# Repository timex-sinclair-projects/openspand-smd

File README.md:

# OpenSpand Card

A chip-down, surface-mount [OpenSpand](https://codeberg.org/NollKollTroll/OpenSpand), the
open-source all-in-one expansion for the Sinclair ZX81, on a card that stands upright in
an edge socket on a ZX81 expansion bus. It's designed for JLCPCB assembly.

The card is 155 × 57 mm, close to the ZX81's width, so a row of cards fits a 3D-printed
case behind the computer. The ZX81's own 23-position edge (key slot at position 3) is cut
along the bottom as gold fingers, 6.38 mm in from the right edge so they line up with the
ZX81's connector. All the SMD parts are on the component side, which faces the ZX81.

| Edge | Connectors |
| --- | --- |
| Left | SPI header (top); DE-9 joystick |
| Right | microSD (card goes in from the side); HDMI (DVI picture, HDMI sound) below it |
| Top | red and green status LEDs (3 mm, hand-fitted, looking up out of the edge); RESET, CONFIG, BOOTSEL and RUN buttons (right-angle, hand-fitted, pushed from above); USB-C |
| Bottom | ZX81 fingers |

**Status: unverified prototype (rev 0.2), fully routed.** Rev 0.2 replaces rev 0.1's VGA
socket with DVI on an HDMI socket, driven by the RP2350's HSTX block, and sends sound over
HDMI ([issue 7](https://github.com/timex-sinclair-projects/openspand-smd/issues/7)). ERC is
clean, the PCB matches the schematic, and DRC shows no clearance, edge or unconnected
errors (only silkscreen warnings). No board has been built, and the firmware patch
deliberately doesn't build until the DVI and HDMI-audio code is written. Review it before
you order.

The full write-up (form factor, finger convention, routing results, regenerating) is in
[card/README.md](card/README.md).

## From modules to chips

Upstream V1.31 is built from plug-in modules plus through-hole parts. The card puts the
chips themselves on a 4-layer board:

| Function | Upstream V1.31 | OpenSpand Card |
| --- | --- | --- |
| MCU | Olimex Pico2-XL module | RP2350B + W25Q128JV 16 MB flash + Abracon ABM8-272-T3 12 MHz crystal |
| 3.3 V | regulator on module | ME6211C33 LDO |
| 1.2 V core | RP2350 switcher + inductor on module | ME6211C12 LDO (no inductor) |
| USB | on module | USB-C, BOOTSEL and RUN buttons |
| RTC | DS1307 module | DS3231MZ (built-in resonator, no crystal) + CR2032 |
| Settings EEPROM (0x50) | AT24C32 on RTC module | FT24C32A |
| I/O expander (0x27) | MCP23009 DIP-18 | MCP23009 SSOP-20 (same chip: 5 V-tolerant open-drain joystick inputs) |
| Audio | UDA1334 module | HDMI audio (firmware not written yet) |
| Composite video | pin header | DVI on an HDMI socket, 60 Hz, via HSTX (firmware not written yet) |
| SD card | full-size SD | microSD (TF-01A push-push) |
| 5 V joystick jumpers | pin-header jumpers | solder jumpers JP1, JP2 (open by default) |
| Serial port | UART header | none (no GPIO left) |

The DS3231MZ answers at the DS1307's address (0x68) with the same time and date
registers, so the firmware's clock code runs unchanged. It shares the I2C bus and pull-ups
with the EEPROM and I/O expander. The CR2032 is only a backup cell; nothing charges it.

## Firmware

The card needs the upstream OpenSpand_SW 0.51.0 firmware with
[card/firmware/card-pins.patch](card/firmware/card-pins.patch) applied, plus a DVI and
HDMI-audio driver that hasn't been written yet. Until then the patch fails to build, on
purpose (see [card/README.md](card/README.md#firmware)). The fingers are on the same side
as the RP2350B, and HSTX, the RP2350's only route to DVI, is fixed to GPIO12..19, so the
card puts the Z80 bus on different GPIOs from upstream:

| GPIO | Card |
| --- | --- |
| 0–7 | D0–D7 |
| 8–11 | A0–A3 |
| 12–19 | HSTX: DVI to the HDMI socket |
| 20–31 | A15–A4 (reversed) |
| 32–39 | HALT, MREQ, IORQ, RD, WR, RESET, M1, RFSH |
| 40–47 | Z80 clock (buffered), green LED, I2C, microSD |

Data still reads as the low byte of the GPIO register, as upstream does. The address comes
from one read of the low register, with a shift for A0..A3 and an RBIT for A4..A15.
GPIO40–47 are the RP2350B's ADC pins, which aren't 5 V tolerant, and the 32 bus lines use
up every other GPIO, so the ZX81's clock reaches GPIO40 through a 74LVC3G34 buffer.

The I2S DAC, its line-out jack and the serial port are gone: HSTX's eight pins took theirs.
The joystick's I/O expander, the clock and the settings EEPROM are unchanged on I2C.

## Ordering from JLCPCB

- **PCB**: upload `card/hardware/fab/OpenSpand-Card-gerbers.zip`. Choose 4 layers, 1.6 mm,
  any colour, and **gold fingers with a 45° bevel**. The tongue has no vias or pour and the
  inner planes stop at the body, so the bevel only cuts the fingers' ends.
- **Assembly**: top side. Upload `BOM-JLCPCB.csv` and `CPL-JLCPCB.csv`, then check every
  part's rotation in JLC's preview, especially U2, U3, U4, U8, U9, U10, U11, J3, J5 and J8.
- **Hand-fit** (`hand-solder.csv`): the DE-9 (J4), the four buttons (SW1–SW4, C&K
  PTS645VL83-2 LFS), the two 3 mm LEDs (D3, D4; bend the legs 90° so they look up out of the
  top edge) and the optional pin header. JLC fits the HDMI socket (J8, Molex
  208658-1001, LCSC C916313).

### Before ordering, check

- **Finger alignment**: the 6.38 mm offset assumes the ZX81's board is centred in its case.
  Measure from the case's right side to the end of the edge connector, subtract 6 mm, set
  `RIGHT_OVERHANG` in `card/tools/gen_pcb.py` and regenerate.
- **Backplane spacing**: the DE-9 stands about 12.5 mm off the board, so sockets on the bus
  need roughly 15 mm or more between them.
- **RP2350 support circuit**: the crystal (ABM8-272-T3, 15 pF load caps, 1 kΩ series
  resistor) follows Raspberry Pi's *Hardware design with RP2350*. The core supply doesn't: the
  on-chip switching regulator is unused (no inductor, VREG_LX open, VREG_FB grounded) and an
  ME6211C12 LDO (U9) feeds DVDD at 1.2 V, as in section 6.3.7 of the RP2350 datasheet. JLC
  may show its generic warning about following Raspberry Pi's guide.
- **HDMI socket**: J8 uses KiCad's footprint for the Molex 208658-1001 (LCSC C916313), with
  its "PCB Edge" line on the board edge. Compare it with Molex's drawing, and check that the
  mouth clears a case wall.
- **TMDS routing**: the eight DVI lines are 0.15 mm tracks over the GND plane, matched
  within a pair but not impedance-controlled. That's normal for GPIO-driven DVI at 640 x 480
  (252 Mbit/s per lane), but no board has been tested.
- **ESD arrays**: U10 and U11 are TI TPD4E05U06DQAR (C138714), flow-through: each TMDS line
  runs straight across a pad pair (1-10, 2-9, 4-7, 5-6).
- **Coin cell**: fit a CR2032 in BT1 after assembly; the board ships without one.
- **Buttons**: SW1–SW4 are C&K PTS645VL83-2 LFS right-angle through-hole switches, marked
  DNP so JLC skips them; buy them from Digi-Key or Mouser (LCSC has only the short-plunger
  PTS645VK39) and solder them yourself.
- **Low-stock parts**: MCP23009T-E/SS (C629436) and FT24C32A (C232883) had a few hundred in
  stock when this was designed.

## Bus board

[ZX81 Bus](bus/README.md) is a passive three-slot backplane for the card: it plugs onto the
ZX81 in the same plane through a card-edge socket straddling its front edge, holds three cards in vertical card-edge sockets, and
repeats the ZX81's edge as gold fingers on its rear edge for a RAM pack or another bus. A 9 V DC jack powers the ZX81 and the bus from a modern supply.

## Earlier board

[OpenSpand SMD2](smd2/README.md) is the same circuit on a 100 × 70 mm board that plugs
straight onto the ZX81's edge connector with a socket, like upstream. The card is based on
it, and it's kept for reference. (The first board, OpenSpand SMD, kept upstream's GPIO map,
which puts A8–A15 on the RP2350B's ADC pins, which aren't 5 V tolerant. It has been
retired; it's in the git history.)

## Repository layout

```
card/                 OpenSpand Card (the main design)
  tools/              design.py is the single source of truth; the other scripts generate
                      the library, schematic, placement, routing and fab files from it
  hardware/           KiCad project, fab/ output
  firmware/           pin-map patch for OpenSpand_SW
  docs/               renders
smd2/                 OpenSpand SMD2, same structure
bus/                  ZX81 Bus, three-slot backplane, same structure
```

The schematics and PCBs are generated: edit `design.py` and regenerate, as described in
[card/README.md](card/README.md#regenerating).

## License

Hardware: CC BY-SA 4.0, as a derivative of OpenSpand HW 1.3.1 by Adam Klotblixt & ZX-Team.
The DE-9 footprint (and SMD2's edge-socket footprint) are copied unchanged from upstream.
The OpenSpand firmware is GPL-3.0 and lives upstream; the firmware patches here are GPL-3.0.

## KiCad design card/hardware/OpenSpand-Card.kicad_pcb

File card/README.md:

# OpenSpand Card

The [SMD2](../smd2/README.md) circuit on a card that stands upright in an edge socket on a
ZX81 expansion bus. The card is 155 mm wide, close to the ZX81's 167 mm, so it can go in a
3D-printed case. It is 57 mm tall: a 49 mm body, plus the fingers.

**Status: unverified prototype (rev 0.2).** No board has been built, and the firmware patch
hasn't been compiled or tested. Rev 0.2 swaps rev 0.1's VGA socket for DVI on an HDMI socket
([issue 7](https://github.com/timex-sinclair-projects/openspand-smd/issues/7)), and the DVI
output has no firmware yet: see [Firmware](#firmware). See [Result](#result) for the routing and
check state.

## Form factor

```
 ┌──────────────────────────────────────────────────────────────────────┐
 │ SPI        ▲R   ▲G     ▲RESET ▲CONFIG ▲BOOT ▲RUN  USB-C       ┌──────┤
 ├─────┐ U4                                                      │ SD  ►│
 │◄DE-9│                                                         ├──────┤
 ├─────┘                                         RP2350B         │HDMI ►│
 │                                                               └──────┤
 └──────────────────────────────┐▌▌ ▌▌▌▌▌▌▌▌▌▌▌▌▌▌▌▌▌▌▌▌┌─────┘
                                └─────────────────────────┘
   seen from the front (the component side, which faces the ZX81)
```

- **Fingers**: the ZX81's own edge, 23 positions at 0.1 in, key slot at position 3
  (2 fingers left of the slot, 20 right of it). Fingers are 1.65 x 7 mm on an 8 mm tongue.
- **Which side is which**: the components face the ZX81. Seen from that side the card
  matches the ZX81's edge seen from above: the front fingers carry the ZX81's top-side
  signals (D7, ~RAMCS, key, D0 ... ~RFSH), and the back fingers carry its underside
  signals (+5V, +9V, key, 0V ... ~ROMCS). Position 1 is on the left. A backplane that
  wires each socket straight through to the ZX81 connector, ZX81 top row to the socket's
  front row, works as-is.
- **Alignment**: the fingers sit 6.38 mm in from the card's right edge. That figure
  assumes the ZX81 board sits centred in its 167 mm case: the board is 142.24 mm wide
  (from the [ZX81+38](https://github.com/mahjongg2/ZX81plus38) drop-in replacement), and
  its edge connector runs to the board's right end. **Measure a real ZX81 before ordering**:
  take the distance from the case's right side (seen from the front) to the end of the
  edge connector, and subtract 6 mm. Set `RIGHT_OVERHANG` in `tools/gen_pcb.py` to the
  result and rerun the pipeline.
- **Connectors**: on the left edge, the SPI header (J6) at the top and the DE-9 joystick port
  below it, with the joystick's I/O expander (U4) just inboard. On the right edge, the microSD
  (the card goes in from the side) above the HDMI socket. Along the top edge: the two status
  LEDs, four buttons and USB-C. There's no SWD header; flash over USB with BOOTSEL.
  The buttons are named on the silkscreen: RESET and CONFIG, as on OpenSpand, plus BOOTSEL
  and RUN for the RP2350B (upstream has BOOTSEL on its Pico module and RUN only as a pin).
  The DE-9 stands about 12.5 mm off the board (the HDMI socket about 6.5 mm), so sockets on
  the backplane need roughly 15 mm or more between them.
- **Buttons through the top of the case**: SW1–SW4 are C&K PTS645VL83-2 LFS right-angle
  through-hole tactile switches, hand-fitted (DNP for JLC). Each has a 3.5 mm plunger pointing
  up out of the top edge. For the case: the body's front is flush with the board edge, the
  plunger tip is about 5.8 mm past it, and the plunger's axis is 3.5 mm above the component
  side. The four sit at 49.5, 62.7, 75.9 and 89.1 mm from the card's left edge (RESET, CONFIG,
  BOOTSEL, RUN). The body is 7.5 mm wide.
- **Status LEDs through the top of the case**: D3 (red) and D4 (green) are 3 mm diffused
  through-hole LEDs (Kingbright WP710A10ID and WP710A10GD), hand-fitted (DNP for JLC). Bend
  the legs 90° about 1.3 mm from the flange so the body lies on the component side and looks
  up out of the top edge, like the buttons: the flange sits 0.7 mm inside the edge, the dome
  about 4.6 mm past it, and the LED's axis is 2 mm above the board. Their centres are 26 and
  36 mm from the card's left edge, 10 mm apart, with about 4 mm clear to H1 and 6 mm to
  RESET. The flat (cathode) side goes to the square pad. Each runs from 3.3 V through 2.2 kΩ
  (R22, R23), about 0.6 mA red and 0.5 mA green: a soft glow from a diffused LED, not a glare.
  For brighter, drop the resistors (not below 330 Ω); for dimmer, raise them.
- **1.2 V core LDO instead of the RP2350's switcher**: an ME6211C12 (U9) feeds DVDD, so there's
  no inductor and none of the switcher's layout rules. The RP2350 datasheet allows this
  (section 6.3.7): VREG_LX is left open, VREG_FB is grounded, and VREG_VIN and VREG_AVDD stay
  powered for the reset and brownout circuits. It's 1.2 V rather than 1.1 V because the
  firmware runs the core at 1.20 V for its 208 MHz overclock. The on-chip regulator still
  starts at power-up but can't drive anything without its inductor; firmware can turn it off
  (VREG.HIZ) to save about 400 µA. The LDO wastes about 0.1 W.
- **DVI on an HDMI socket instead of composite video**: the RP2350's HSTX block, which can
  only drive GPIO12..19, sends DVI (TMDS) to an HDMI type A socket (J8, Molex 208658-1001) on
  the right edge. Each of the eight lines goes through 220 Ω (R24–R31), as on Adafruit's DVI
  Sock and HSTX adapter, and then through a flow-through ESD array (U10, U11, TPD4E05U06) at
  the socket. Pin 18 gets +5V through a Schottky (D5), which some displays need before they'll
  take a picture. DDC, CEC and hot-plug detect are left open: DDC pulls up to 5 V and the free
  GPIOs aren't 5 V tolerant. HSTX can put any lane or the clock, of either polarity, on any of
  its pins, so the pairs are wired in the order the socket's pins come.
- **Sound over HDMI, no line-out or serial port**: HSTX needs eight GPIOs, and the Z80 bus
  needs every other 5 V-tolerant one, so the I2S DAC (and its line-out jack) and the UART
  header are gone; the firmware is to send sound as HDMI audio. The DE-9's I/O expander,
  the real-time clock and the settings EEPROM stay on I2C exactly as in rev 0.1.
- **Bus pins round HSTX**: only GPIO0..39 are 5 V tolerant, and with HSTX on GPIO12..19 the 32
  bus lines take every one of the rest. D0..D7 stay on GPIO0..7 and A0..A3 on GPIO8..11.
  A15..A4 are on GPIO20..31, in reverse, so their tracks fan out to the fingers without
  crossing, and the control lines are on GPIO32..39. Z80_CLK goes to GPIO40 (an ADC pin)
  through one gate of a 74LVC3G34 (U8), whose inputs take 5 V. The red LED (D3) is on the
  I/O expander's GP2 as in rev 0.1, and the green LED (D4) is on GPIO41.
- **Real-time clock**: a DS3231MZ (U5) at 0x68 in place of SMD2's DS1307. It has a
  built-in MEMS resonator, so there's no 32.768 kHz crystal, and it keeps time to about
  ±5 ppm (a few minutes a year). It uses the DS1307's address and time registers, so the
  firmware's `GET TIM` / `GET DAT` and time and date screens work unchanged. Backup is a
  plain CR2032 (BT1) that slides in from the bottom edge; there's no charger.
- **Five M3 holes** (3.2 mm, unplated) for screw posts in a case: top left, between the SPI
  header and the LEDs (H1); lower left corner (H3); top right corner, above the microSD (H4); bottom right, in
  the corner below the HDMI socket (H5); and one near the bottom middle (H2).

## What changed from SMD2

| | SMD2 | Card |
| --- | --- | --- |
| Board | 100 x 70 mm, socket on the bottom edge | 155 x 57 mm card with gold fingers |
| ZX81 connection | edge socket (plugs onto the ZX81) | fingers (stand in a socket on a bus) |
| Video | composite, 2-pin header J8 | DVI on an HDMI socket J8 (HSTX) |
| Audio | I2S DAC, line-out jack | over HDMI (firmware); no DAC or jack |
| DE-9 | bottom side | top side, left edge |
| Serial port (UART) | GPIO40-41, header J10 | none |
| Red LED | GPIO38 (PWM, also sampled audio) | I/O expander GP2 (on/off only) |
| Green LED | GPIO39 | GPIO41 |
| Headers | SWD, UART, SPI, digitized audio | SPI only |
| Real-time clock | DS1307 + 32.768 kHz crystal + CR2032 | DS3231MZ (no crystal) + CR2032 |
| RP2350 core supply | on-chip switcher + 3.3 µH inductor | ME6211C12 LDO at 1.2 V |
| Buttons | top-push SMD, inboard | right-angle THT on the top edge, hand-fitted |
| GPIO0..7 | control lines | D0..D7 |
| GPIO8..11 | A0..A3 | same |
| GPIO12..19 | A4..A11 | HSTX (DVI) |
| GPIO20..31 | A12..A15, D0..D7 | A15..A4 |
| GPIO32..39 | Z80 clock, I2S, video, LEDs | control lines |
| GPIO40..47 | UART, I2C, microSD | Z80 clock (buffered), green LED, I2C, microSD |

**Why the bus moves.** On SMD2 the edge socket is on the bottom of the board. Here the
fingers are on the same side as the RP2350B, which mirrors the left-to-right order. With
U2 turned 90° its GPIO0..31 sweep round its lower-left corner, along its bottom edge toward
the fingers and up its right side. HSTX sits in the middle of that bottom edge (GPIO12..19),
so the bus goes round it: data and A0..A3 to its left, the rest of the address bus up U2's
right side, and the control lines along its top edge. The DVI pairs leave U2's bottom edge
and run right to the HDMI socket, under the address lines, which reach the fingers on
B.Cu.

## Result

Fully routed on four layers (signal, GND, power, signal). DRC with schematic parity and a
zone refill reports no copper, clearance, edge or unconnected errors; what remains is
silkscreen only (reference text over copper, overlapping or near the edge), which the fab
clips. ERC is clean.

| | Card rev 0.2 | Card rev 0.1 | SMD2 |
| --- | --- | --- | --- |
| Vias | 250 | 301 | 268 |
| Signal vias | 118 | 150 | 126 |
| Track length | 3367 mm | 3545 mm | 3520 mm |
| Z80 bus track | 1174 mm | 1095 mm | 1319 mm |

The Z80 bus is shorter than on SMD2 because the fingers run right under U2. Rev 0.2 has less
track and fewer vias than rev 0.1 because the audio DAC, line out and UART header at the
left end are gone. The eight TMDS lines are 23 to 26 mm long with no vias; the two halves of
each pair are within 0.5 mm of each other. Freerouting closed every connection (the first
run left RUN open, and a second run with 200 passes closed it), and no signal runs on the
inner planes. The only inner-layer copper is the +1V2 core rail, a short spur on In2 as on
SMD2. The silkscreen warnings went up from rev 0.1 (mostly references overlapping in the
column of 0402 resistors). The fab clips silkscreen off exposed copper.

## Firmware

`firmware/card-pins.patch` applies to upstream OpenSpand_SW 0.51.0, like SMD2's patch:

```bash
cd OpenSpand/OpenSpand_SW
patch -p1 < /path/to/card/firmware/card-pins.patch
```

It moves every pin to the rev 0.2 map in `firmware/pins.h`. Data reads and writes still use
the low byte of the GPIO registers, exactly as upstream. The address read becomes
`((lo >> 8) & 0x000F) | ((__rbit(lo) << 4) & 0xFFF0)` on one read of the low GPIO
register: A0..A3 sit on GPIO8..11 and A4..A15 on GPIO31..20, reversed, which RBIT (one
instruction on the Cortex-M33) undoes. The video PIO gets GPIO base 16, and Z80_CLK, now
on GPIO40, is index 24 in that window, the same encoding as upstream's GPIO24. SMD2's
[checklist](../smd2/README.md#firmware) applies: timing, and SDK pin handling with a GPIO base.

**The patch doesn't build yet, on purpose.** Rev 0.2 has no composite video, I2S DAC or
serial port, so `pins.h` leaves `VIDEO_SYNC`, `VIDEO_DATA`, `I2S_PIN_*`, `ZX_SER_TX`,
`ZX_SER_RX` and `LED_RED` undefined. Code that still uses them fails to compile instead of
driving a bus pin. What's needed:

- **DVI out over HSTX**, in place of the composite video PIO: core 1 already hands each ZX81
  pixel byte to the video PIO, so it stores it in a line buffer instead, and HSTX, fed by
  DMA with its TMDS encoder on, sends 640 x 480 at 60 Hz, each ZX81 line twice. HSTX bit n
  is GPIO12+n; `HSTX_PIN_n` in `pins.h` says which TMDS line each one is. The lanes go
  D0 on bits 3/2, D1 on 5/4, D2 on 7/6 and the clock on 1/0, positive on the odd bit.
  [Adafruit DVI HSTX](https://github.com/adafruit/Adafruit-DVI-HSTX) and the Pico SDK's
  `dvi_out_hstx_encoder` example both set this up. The DMA interrupt has to go on core 0,
  since core 1 is servicing the Z80 bus. HSTX needs about 126 MHz (25.2 MHz pixels, ten
  bits each, two per HSTX clock), and the firmware's 208 MHz system clock doesn't divide
  down to that. The usual fix is a 252 MHz system clock with HSTX at half of it, and that
  has to be checked against the bus timing, which was tuned at 208 MHz.
- **Sound as HDMI audio**: the AY and beeper output that went to I2S goes into HDMI data
  islands instead, as in [pico_hdmi](https://github.com/fliperama86/pico_hdmi) and
  [frank-hdmi-audio](https://github.com/rh1tech/frank-hdmi-audio). Strictly this sends HDMI
  rather than DVI, which every HDMI display takes. A DVI-only monitor shows the picture and
  stays silent.
- **No serial port**: the serial commands (ports 0xE3 / 0xEB, `OPEN SERIAL`, `OPEN MIDI`,
  `PUT SER`) and the ZXpand serial server have nowhere to go.
- **Red LED**: bit 2 of the I/O expander at 0x27, active low, as in rev 0.1; the green LED
  is on GPIO41.

## Regenerating

From `tools/`:

```bash
python3 gen_lib.py      # project library: edge fingers, Z80_CLK buffer, ESD arrays (and the SMD2 parts)
python3 gen_sch.py
KPY=/Applications/KiCad/KiCad.app/Contents/Frameworks/Python.framework/Versions/Current/bin/python3
$KPY gen_pcb.py
FREEROUTING_JAR=~/freerouting.jar JAVA=/opt/homebrew/opt/openjdk/bin/java $KPY route.py 150
$KPY finish.py
python3 export_fab.py
```

The schematic and PCB are generated: to change the circuit, edit `design.py` and
regenerate. `route.py` starts from the unrouted board, so run `gen_pcb.py` before it every
time. Routing takes 5 to 10 minutes. The result varies a little from run to run, so a fresh
run can still end with an open connection; `finish.py` reports any it couldn't close.
`route.py reuse` re-imports the last run's `.ses` file without routing again, which is
useful after a rule-only change in `gen_pcb.py`.

### How the board is routed

- **Planes.** In1 is solid GND and In2 is +3V3, over the body only. Every SMD GND and +3V3
  pad gets a short track and a via to its plane. The RP2350B's supply pins put their vias
  inward, in the ring between the pins and the exposed pad, so the outside is free for
  signals.
- **1.2 V core.** The RP2350B's core supply (+1V2) is fanned out the same way and joined by
  a 0.3 mm track tree on In2, cut into the +3V3 plane.
- **Fingers.** A rule area over the tongue bans vias and pours. The GND fingers (on the
  back) are tied to the plane by a short stub and a via just above the tongue.
- **Pre-routes.** VREG_AVDD, the QSPI flash bus and the USB
  pair are maze-routed before the autorouter runs, because they're boxed in around the
  RP2350B. So are the eight TMDS lines, from U2's HSTX pins through R24..R31 and the ESD
  arrays to the HDMI socket, innermost first, so they run side by side on F.Cu with no
  vias and each pair matched to within about 0.5 mm. Left to Freerouting, they wandered
  round U2 with up to 27 mm between the two halves of a pair.
- **Autoroute.** Freerouting routes everything else on F.Cu and B.Cu.
- **Finishing.** `finish.py` reads the open connections from KiCad's DRC and maze-routes
  each one. When a connection is blocked it rips up nearby nets, routes the blocked one, and
  reroutes the ripped ones, keeping a change only if the count of open connections drops.
  It may run a short track on an inner plane (In1 first, In2 only as a last resort) and
  rejects any route that splits a plane. It then nudges tracks off the board edge, trims
  dangling ends and moves vias a few µm clear where DRC asks.
- **Ground pours.** GND is poured solid on both outer layers.
- **Rules.** Signals use 0.127 mm tracks and gaps (JLC's 4-layer minimum is 0.09 mm), and
  vias are 0.45/0.25 mm.

## Ordering

Fab files go to `hardware/fab/`: `OpenSpand-Card-gerbers.zip`, `BOM-JLCPCB.csv`,
`CPL-JLCPCB.csv` and `hand-solder.csv`. Ordering is as in the
[main README](../README.md#ordering-from-jlcpcb), plus:

- **Gold fingers**: choose "Gold fingers: Yes" and a 45° bevel. JLCPCB's gold-finger option
  plates the fingers with hard gold, which wears far better than ENIG in a socket.
- The tongue has no vias and no copper pour, and the inner planes stop at the body, so the
  bevel cuts nothing but the fingers' ends.
- Hand-fit: DE-9 (J4), the four buttons (SW1–SW4, C&K PTS645VL83-2 LFS), the two 3 mm
  LEDs (D3, D4) and the optional pin header. The HDMI socket (J8, Molex 208658-1001, LCSC C916313) is SMD with through-hole
  shell tabs, so JLC fits it; it uses KiCad's own footprint for that part.

## License

Hardware: CC BY-SA 4.0, as a derivative of OpenSpand HW 1.3.1 by Adam Klotblixt & ZX-Team.
The firmware patch modifies GPL-3.0 code from OpenSpand_SW and is GPL-3.0.

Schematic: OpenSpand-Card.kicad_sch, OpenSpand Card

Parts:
BT1: CR2032; BatteryHolder_Keystone_3034_1x20mm; MPN Keystone 3034TR; LCSC C5213768
C1: 22u; C_0805_2012Metric; LCSC C45783
C2, C3, C4, C35: 10u; C_0805_2012Metric; LCSC C15850
C5, C46: 1u; C_0603_1608Metric; LCSC C15849
C10, C11, C12, C13, C14, C15, C16, C17, C18, C19, C20, C24, C25, C26, C29, C30, C31, C32, C33, C34, C45: 100n; C_0603_1608Metric; LCSC C14663
C21, C22, C23: 4.7u; C_0603_1608Metric; LCSC C19666
C27, C28: 15p; C_0603_1608Metric; LCSC C1644
D1, D2, D5: B5819W; D_SOD-123; LCSC C8598
D3: Red; LED_LiteOn_LTST-S270; MPN LTST-S270KRKT; LCSC C125114
D4: Green; LED_LiteOn_LTST-S270; MPN LTST-S270KGKT; LCSC C125113
H1, H2, H3, H4, H5: M3; MountingHole_3.2mm_M3
J1: ZX81 edge; ZX81_EdgeFingers
J3: USB-C; USB_C_Receptacle_HRO_TYPE-C-31-M-12; LCSC C165948
J4: Joystick; DSUB-9_Male_Horizontal_P2.77x2.84mm_EdgePinOffset4.94mm_Hou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
J5: microSD; TF-01A; LCSC C91145
J6: External SPI; PinHeader_2x03_P2.54mm_Vertical; not fitted
J8: HDMI; HDMI_A_Molex_208658-1001_Horizontal; MPN Molex 2086581001; LCSC C916313
JP1: 5V pin 7; SolderJumper-2_P1.3mm_Open_RoundedPad1.0x1.5mm
JP2: 5V pin 5; SolderJumper-2_P1.3mm_Open_RoundedPad1.0x1.5mm
R1: 33; R_0603_1608Metric; LCSC C23140
R2, R4, R22, R23: 1k; R_0603_1608Metric; LCSC C21190
R3, R11, R12, R13, R14, R15: 10k; R_0603_1608Metric; LCSC C25804
R5, R6: 5.1k; R_0603_1608Metric; LCSC C23186
R7, R8: 27; R_0603_1608Metric; LCSC C25190
R9, R10: 4.7k; R_0603_1608Metric; LCSC C23162
R24, R25, R26, R27, R28, R29, R30, R31: 220; R_0402_1005Metric; LCSC C25091
SW1: Reset; SW_Tactile_SPST_Angled_PTS645Vx83-2LFS; MPN C&K PTS645VL83-2 LFS; not fitted
SW2: RUN; SW_Tactile_SPST_Angled_PTS645Vx83-2LFS; MPN C&K PTS645VL83-2 LFS; not fitted
SW3: BOOTSEL; SW_Tactile_SPST_Angled_PTS645Vx83-2LFS; MPN C&K PTS645VL83-2 LFS; not fitted
SW4: Config; SW_Tactile_SPST_Angled_PTS645Vx83-2LFS; MPN C&K PTS645VL83-2 LFS; not fitted
U1: ME6211C33M5G; SOT-23-5; LCSC C82942
U2: RP2350B; QFN-80-1EP_10x10mm_P0.4mm_EP3.4x3.4mm; LCSC C42415655
U3: W25Q128JVSIQ; SOIC-8_5.3x5.3mm_P1.27mm; LCSC C97521
U4: MCP23009-E/SS; SSOP-20_5.3x7.2mm_P0.65mm; LCSC C629436
U5: DS3231MZ+TRL; SOIC-8_3.9x4.9mm_P1.27mm; LCSC C107410
U6: FT24C32A; SOIC-8_3.9x4.9mm_P1.27mm; LCSC C232883
U8: SN74LVC3G34DCUR; VSSOP-8_2.3x2mm_P0.5mm; LCSC C130024
U9: ME6211C12M5G-N; SOT-23-5; LCSC C236672
U10, U11: TPD4E05U06DQAR; USON-10_2.5x1.0mm_P0.5mm; LCSC C138714
Y1: 12MHz; Crystal_SMD_3225-4Pin_3.2x2.5mm; MPN ABM8-272-T3; LCSC C20625731

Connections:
/5VZX: D1.2 (A), J1.A5 (~ROMCS), J1.A27 (+5V), J1.C26 (~RAMCS)
/+1V2: C18.1, C19.1, C20.1, C21.1, U2.10 (DVDD), U2.32 (DVDD), U2.51 (DVDD), U9.5 (V_{OUT})
/+3V3: C3.1, C4.1, C10.1, C11.1, C12.1, C13.1, C14.1, C15.1, C16.1, C17.1, C22.1, C24.1, C25.1, C26.1, C30.1, C31.1, C32.1, C33.1, C34.1, C35.1, C45.1, C46.1, J5.4 (VDD), R1.1, R3.1, R9.1, R10.1, R11.1, R12.1, R13.1, R14.1, R15.1, R22.1, U1.5 (V_{OUT}), U2.5 (IOVDD), U2.15 (IOVDD), U2.24 (IOVDD), U2.29 (IOVDD), U2.41 (IOVDD), U2.50 (IOVDD), U2.59 (ADC_AVDD), U2.60 (IOVDD), U2.64 (VREG_VIN), U2.68 (USB_OTP_VDD), U2.69 (QSPI_IOVDD), U2.76 (IOVDD), U3.8 (VCC), U4.1 (VDD), U4.5 (ADDR), U4.6 (~RESET), U5.2 (VCC), U6.8 (VCC), U8.8 (VCC), U9.1 (V_{IN}), U9.3 (CE)
/+5V: C1.1, C2.1, D1.1 (K), D2.1 (K), D5.2 (A), J6.5, JP1.1 (A), JP2.1 (A), U1.1 (V_{IN}), U1.3 (CE)
/BOOT: R4.2, SW3.1
/CONFIG: SW4.1, U4.8 (GP0)
/GND: BT1.2 (-), C1.2, C2.2, C3.2, C4.2, C5.2, C10.2, C11.2, C12.2, C13.2, C14.2, C15.2, C16.2, C17.2, C18.2, C19.2, C20.2, C21.2, C22.2, C23.2, C24.2, C25.2, C26.2, C27.2, C28.2, C29.2, C30.2, C31.2, C32.2, C33.2, C34.2, C35.2, C45.2, C46.2, J1.A23 (0V), J1.A24 (0V), J3.A1 (GND), J3.A12 (GND), J3.B1 (GND), J3.B12 (GND), J3.SH (SHIELD), J4.0 (SHIELD), J4.8 (GND), J5.6 (VSS), J5.10 (SHIELD), J5.11 (SHIELD), J5.12 (SHIELD), J5.13 (SHIELD), J6.3, J8.2 (D2S), J8.5 (D1S), J8.8 (D0S), J8.11 (CKS), J8.17 (GND), J8.SH, R5.2, R6.2, R23.2, SW1.2, SW2.2, SW3.2, SW4.2, U1.2 (V_{SS}), U2.62 (VREG_PGND), U2.65 (VREG_FB), U2.81 (GND), U3.4 (GND), U4.20 (VSS), U5.5 (GND), U6.1 (A0), U6.2 (A1), U6.3 (A2), U6.4 (GND), U6.7 (WP), U8.3 (2A), U8.4 (GND), U8.6 (3A), U9.2 (V_{SS}), U10.3 (GND), U10.8 (GND), U11.3 (GND), U11.8 (GND), Y1.2 (G), Y1.4 (G)
/HDMI_5V: D5.1 (K), J8.18 (+5V)
/HSTX_CKN: R31.1, U2.11 (GPIO12)
/HSTX_CKP: R30.1, U2.12 (GPIO13)
/HSTX_D0N: R29.1, U2.13 (GPIO14)
/HSTX_D0P: R28.1, U2.14 (GPIO15)
/HSTX_D1N: R27.1, U2.16 (GPIO16)
/HSTX_D1P: R26.1, U2.17 (GPIO17)
/HSTX_D2N: R25.1, U2.18 (GPIO18)
/HSTX_D2P: R24.1, U2.19 (GPIO19)
/I2C_SCL: R10.2, U2.54 (GPIO43/ADC3), U4.3 (SCL), U5.8 (SCL), U6.6 (SCL)
/I2C_SDA: R9.2, U2.53 (GPIO42/ADC2), U4.4 (SDA), U5.7 (SDA), U6.5 (SDA)
/JOY_D: J4.2 (DOWN), U4.16 (GP6)
/JOY_F: J4.6 (FIRE), U4.13 (GP3)
/JOY_L: J4.3 (LEFT), U4.15 (GP5)
/JOY_P5: J4.5, JP2.2 (B)
/JOY_P7: J4.7, JP1.2 (B)
/JOY_R: J4.4 (RIGHT), U4.14 (GP4)
/JOY_U: J4.1 (UP), U4.17 (GP7)
/LED_GREEN: D4.2 (A), U2.52 (GPIO41/ADC1)
/LED_G_K: D4.1 (K), R23.1
/LED_RED: D3.1 (K), U4.12 (GP2)
/LED_R_A: D3.2 (A), R22.2
/QSPI_SCLK: U2.71 (QSPI_SCLK), U3.6 (CLK)
/QSPI_SD0: U2.72 (QSPI_SD0), U3.5 (DI/IO_{0})
/QSPI_SD1: U2.74 (QSPI_SD1), U3.2 (DO/IO_{1})
/QSPI_SD2: U2.73 (QSPI_SD2), U3.3 (~WP/IO_{2})
/QSPI_SD3: U2.70 (QSPI_SD3), U3.7 (~HOLD/~RESET/IO_{3})
/QSPI_SS: R4.1, U2.75 (~QSPI_SS), U3.1 (~CS)
/RUN: C29.1, R3.2, SW2.1, U2.35 (RUN)
/SD_CLK: J5.5 (CLK), J6.4, U2.57 (GPIO46/ADC6)
/SD_CS: J5.2 (DAT3/CS), R11.2, U2.56 (GPIO45/ADC5)
/SD_DAT1: J5.8 (DAT1), R14.2
/SD_DAT2: J5.1 (DAT2), R15.2
/SD_MISO: J5.7 (DAT0/DO), J6.2, R13.2, U2.55 (GPIO44/ADC4)
/SD_MOSI: J5.3 (CMD/DI), J6.6, R12.2, U2.58 (GPIO47/ADC7)
/SPI_CS: J6.1, U4.9 (GP1)
/TMDS_CKN: J8.12 (CK-), R31.2, U11.5 (IO4), U11.6 (IO4)
/TMDS_CKP: J8.10 (CK+), R30.2, U11.4 (IO3), U11.7 (IO3)
/TMDS_D0N: J8.9 (D0-), R29.2, U11.2 (IO2), U11.9 (IO2)
/TMDS_D0P: J8.7 (D0+), R28.2, U11.1 (IO1), U11.10 (IO1)
/TMDS_D1N: J8.6 (D1-), R27.2, U10.5 (IO4), U10.6 (IO4)
/TMDS_D1P: J8.4 (D1+), R26.2, U10.4 (IO3), U10.7 (IO3)
/TMDS_D2N: J8.3 (D2-), R25.2, U10.2 (IO2), U10.9 (IO2)
/TMDS_D2P: J8.1 (D2+), R24.2, U10.1 (IO1), U10.10 (IO1)
/USB_CC1: J3.A5 (CC1), R5.1
/USB_CC2: J3.B5 (CC2), R6.1
/USB_C_DM: J3.A7 (D-), J3.B7 (D-), R8.1
/USB_C_DP: J3.A6 (D+), J3.B6 (D+), R7.1
/USB_DM: R8.2, U2.66 (USB_DM)
/USB_DP: R7.2, U2.67 (USB_DP)
/VBAT: BT1.1 (+), U5.6 (VBAT)
/VBUS: D2.2 (A), J3.A4 (VBUS), J3.A9 (VBUS), J3.B4 (VBUS), J3.B9 (VBUS)
/VREG_AVDD: C23.1, R1.2, U2.61 (VREG_AVDD)
/XIN: C27.1, U2.30 (XIN), Y1.1
/XOUT: R2.1, U2.31 (XOUT)
/XOUT_X: C28.1, R2.2, Y1.3
/Z80_A0: J1.A21 (A0), U2.6 (GPIO8)
/Z80_A1: J1.A20 (A1), U2.7 (GPIO9)
/Z80_A2: J1.A19 (A2), U2.8 (GPIO10)
/Z80_A3: J1.A18 (A3), U2.9 (GPIO11)
/Z80_A4: J1.A6 (A4), U2.39 (GPIO31)
/Z80_A5: J1.A7 (A5), U2.38 (GPIO30)
/Z80_A6: J1.A8 (A6), U2.37 (GPIO29)
/Z80_A7: J1.A9 (A7), U2.36 (GPIO28)
/Z80_A8: J1.A10 (A8), U2.28 (GPIO27)
/Z80_A9: J1.A11 (A9), U2.27 (GPIO26)
/Z80_A10: J1.A12 (A10), U2.26 (GPIO25)
/Z80_A11: J1.A13 (A11), U2.25 (GPIO24)
/Z80_A12: J1.A14 (A12), U2.23 (GPIO23)
/Z80_A13: J1.A15 (A13), U2.22 (GPIO22)
/Z80_A14: J1.A16 (A14), U2.21 (GPIO21)
/Z80_A15: J1.A17 (A15), U2.20 (GPIO20)
/Z80_CLK: J1.A22 (CLK), U8.1 (1A)
/Z80_CLK_3V3: U2.49 (GPIO40/ADC0), U8.7 (1Y)
/Z80_D0: J1.C24 (D0), U2.77 (GPIO0)
/Z80_D1: J1.C23 (D1), U2.78 (GPIO1)
/Z80_D2: J1.C22 (D2), U2.79 (GPIO2)
/Z80_D3: J1.C19 (D3), U2.80 (GPIO3)
/Z80_D4: J1.C18 (D4), U2.1 (GPIO4)
/Z80_D5: J1.C20 (D5), U2.2 (GPIO5)
/Z80_D6: J1.C21 (D6), U2.3 (GPIO6)
/Z80_D7: J1.C27 (D7), U2.4 (GPIO7)
/Z80_HALT: J1.C15 (~HALT), U2.40 (GPIO32)
/Z80_IORQ: J1.C13 (~IORQ), U2.43 (GPIO34)
/Z80_M1: J1.C6 (~M1), U2.47 (GPIO38)
/Z80_MREQ: J1.C14 (~MREQ), U2.42 (GPIO33)
/Z80_RD: J1.C12 (~RD), U2.44 (GPIO35)
/Z80_RFSH: J1.C5 (~RFSH), U2.48 (GPIO39)
/Z80_RST: C5.1, J1.C7 (~RESET), SW1.1, U2.46 (GPIO37)
/Z80_WR: J1.C11 (~WR), U2.45 (GPIO36)

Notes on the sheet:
Power
ZX81 bus
MCU
USB
I2C
SD card
Video & I/O
Mechanical

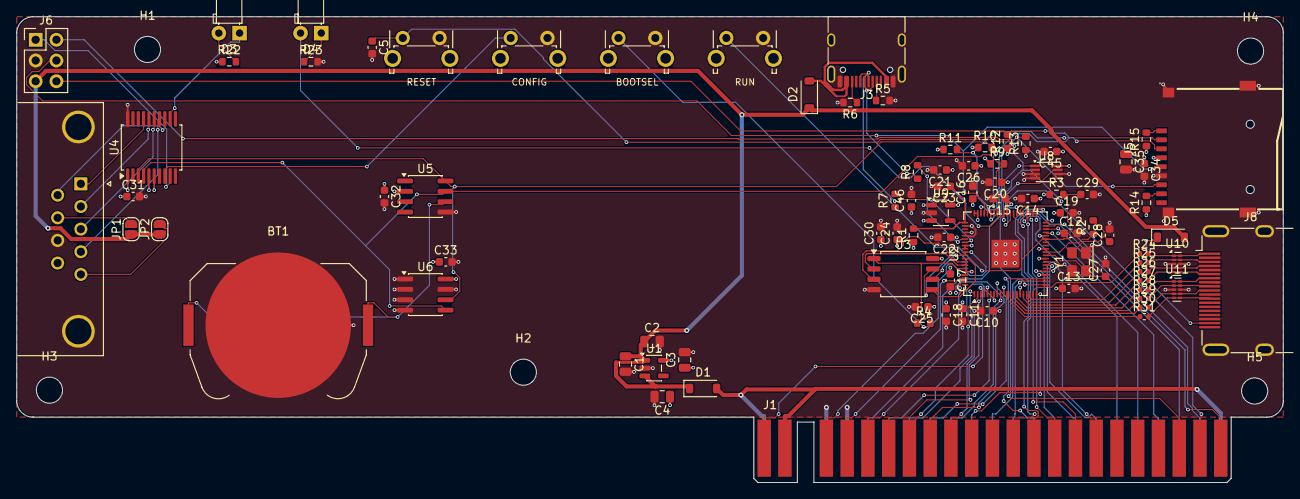
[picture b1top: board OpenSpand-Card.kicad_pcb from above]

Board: 4 copper layers, 155.0 x 57.0 mm, 92 parts (0 on the bottom side), 97 nets.

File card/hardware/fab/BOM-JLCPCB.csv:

Comment,Designator,Footprint,LCSC Part #
CR2032,BT1,BatteryHolder_Keystone_3034_1x20mm,C5213768
22u,C1,C_0805_2012Metric,C45783
100n,"C10,C11,C12,C13,C14,C15,C16,C17,C18,C19,C20,C24,C25,C26,C29,C30,C31,C33,C32,C34,C45",C_0603_1608Metric,C14663
10u,"C2,C3,C4,C35",C_0805_2012Metric,C15850
4.7u,"C22,C23,C21",C_0603_1608Metric,C19666
15p,"C27,C28",C_0603_1608Metric,C1644
1u,"C5,C46",C_0603_1608Metric,C15849
B5819W,"D1,D2,D5",D_SOD-123,C8598
USB-C,J3,USB_C_Receptacle_HRO_TYPE-C-31-M-12,C165948
microSD,J5,TF-01A,C91145
HDMI,J8,HDMI_A_Molex_208658-1001_Horizontal,C916313
33,R1,R_0603_1608Metric,C23140
1k,"R2,R4",R_0603_1608Metric,C21190
2.2k,"R22,R23",R_0603_1608Metric,C4190
220,"R24,R25,R26,R27,R28,R29,R30,R31",R_0402_1005Metric,C25091
10k,"R3,R11,R12,R13,R14,R15",R_0603_1608Metric,C25804
5.1k,"R5,R6",R_0603_1608Metric,C23186
27,"R7,R8",R_0603_1608Metric,C25190
4.7k,"R9,R10",R_0603_1608Metric,C23162
ME6211C33M5G,U1,SOT-23-5,C82942
TPD4E05U06DQAR,"U10,U11",USON-10_2.5x1.0mm_P0.5mm,C138714
RP2350B,U2,QFN-80-1EP_10x10mm_P0.4mm_EP3.4x3.4mm,C42415655
W25Q128JVSIQ,U3,SOIC-8_5.3x5.3mm_P1.27mm,C97521
MCP23009-E/SS,U4,SSOP-20_5.3x7.2mm_P0.65mm,C629436
DS3231MZ+TRL,U5,SOIC-8_3.9x4.9mm_P1.27mm,C107410
FT24C32A,U6,SOIC-8_3.9x4.9mm_P1.27mm,C232883
SN74LVC3G34DCUR,U8,VSSOP-8_2.3x2mm_P0.5mm,C130024
ME6211C12M5G-N,U9,SOT-23-5,C236672
12MHz,Y1,Crystal_SMD_3225-4Pin_3.2x2.5mm,C20625731

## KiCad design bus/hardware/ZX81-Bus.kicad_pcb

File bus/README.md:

# ZX81 Bus

A passive three-slot backplane for the ZX81. It plugs onto the ZX81's edge connector in
the same plane as the ZX81's board, holds three cards such as the [OpenSpand Card](../card/README.md) upright in card-edge
sockets, and repeats the ZX81's edge as gold fingers on its rear edge, so a RAM pack, a
printer interface or another bus board can plug on behind it. A 9 V DC jack on the right
lets a modern power supply run the ZX81 and the bus.

**Status: unverified prototype (rev 0.1).** ERC is clean, the PCB matches the schematic,
and DRC reports only two silkscreen warnings: the DC jack's outline runs past the right
edge, where the jack overhangs on purpose. No board has been built.

## Layout

```
          ┌─┐ rear fingers: a copy of the ZX81 edge (C row on top)
   ┌──────┘ └──────┐
   │ ▭▭▭ SLOT 3 J4 │
   │ ▭▭▭ SLOT 2 J3 │   cards stand here, component side toward the ZX81
   │ ▭▭▭ SLOT 1 J2 │
   │          J6 ◧═│   9 V DC jack, opening to the right
   │ ▮▮▮ J1 ▮▮▮    │   pads for the socket that straddles the front edge
   └───[socket]────┘
          ZX81       same plane as the bus board
   seen from above, standing in front of the ZX81
```

- **Board**: 85 x 78.5 mm: an 85 x 70.5 mm body plus the 8 mm rear tongue. Four layers:
  F.Cu and B.Cu carry the bus, In1 is a solid GND plane and In2 a +5V plane. The body
  runs from 7 mm left of the slots (room for the holes) to 12 mm right of them (room for
  the DC jack); `X0` and `XR` in `tools/gen_pcb.py` set the sides.
- **J1** is a row of pads on each side of the front edge for a straddle-mounted socket:
  take a 2 x 23, 0.1 in card-edge socket, bend its tails in (about 30°) so they pinch the
  board, and solder them to the pads. The socket sticks out of the front edge and takes
  the ZX81's fingers, so the bus board lies in the same plane as the ZX81's board. The
  pads are 1.65 x 7 mm, the same as the rear fingers, starting 0.3 mm in from the edge
  (JLC's minimum copper-to-edge clearance): the top row (C) on F.Cu, the
  bottom row (A) on B.Cu. Position 3 (the key) has pads with no net, for soldering a tail
  there for strength if the socket has one. The front edge is straight; only the rear
  edge has a tongue.
- **J2-J4** are vertical card-edge sockets: 2 x 23 positions at 0.1 in (the same centres as
  the fingers), rows 0.2 in apart, key at position 3. Position 3 has plated holes with no
  net, so a socket with all 46 tails fits, keyed or not. Holes are 1.0 mm on 1.5 mm pads.
- **Slot pitch** is 0.8 in (20.32 mm). The card's DE-9 and VGA socket stand about 12.5 mm
  off its component side, and the card's README asks for at least 15 mm. `SLOT_PITCH` in
  `tools/gen_pcb.py` sets it.
- **J5**, the rear fingers, match the card's: 1.65 x 7 mm on an 8 mm tongue, key slot at
  position 3, no vias or pour on the tongue, and the inner planes stop at the body.
- **J6**, a 5.5/2.1 mm DC jack, tip positive, on the ZX81's +9V line. It sits in the
  front-right corner between J1 and slot 1, with its opening 0.5 mm past the right edge so
  an enclosure wall can sit flush with it. Its footprint is KiCad's CUI PJ-102AH (round
  holes: centre pin at the back, sleeve, and the switch pin, left unconnected).
- **D1**, an SS34 Schottky (3 A, 40 V, SMA, LCSC C8678), in series from the jack's centre
  pin to +9V, in front of the jack. A centre-negative supply is blocked instead of putting
  -9 V on the ZX81. It drops about 0.4 V, which the ZX81's 7805 doesn't mind at 9 V.
  From D1's cathode, the +9V run is at the far left (position 2), and the bus runs cover
  both outer layers, so the feed crosses on In2 as a 1 mm track cut into the +5V plane,
  just behind J1's pads, and comes up through a via beside the +9V run.
- **Five M3 holes** (3.2 mm) for an enclosure: three down the left edge (between the slots
  and beside the jack) and two down the right edge, between the slots.

## Which way round

Every connector has position 1 on the left (seen from above, standing in front of the
ZX81), and position *n* of every connector sits at the same x, so each signal is one
straight run from front to back:

- **C row** (the ZX81's top side: D7, ~RAMCS, key, D0 ... ~RFSH) on F.Cu. The
  straddle socket's top contacts touch the ZX81's top side and its top tails solder to
  the top pads. On each slot it is the front row, nearer the ZX81, so a card's component
  side faces the ZX81, as the card is designed. On the rear tongue it is on the top, as
  on the ZX81.
- **A row** (the underside: +5V, +9V, key, 0V ... ~ROMCS) on B.Cu: the slots' rear row and
  the bottom of the rear tongue.

Where a run meets the other row's hole at a slot, it steps half a pitch sideways and
back. At J1 there are no holes, so the runs start straight from the pads. No autorouter
is needed; `gen_pcb.py` draws every track. Signals are 0.3 mm,
+5V, +9V and GND 0.6 mm, with 0.2 mm clearance. +5V also feeds the In2 plane through
vias between the connectors.

## Check before ordering

- **Which end is position 1.** Everything rests on the card's statement that, seen from
  above with the ZX81 in front of you, the ZX81's key slot is near the left end of its
  edge. Check it on the machine. If the key is at the right end, every connector here must
  be mirrored before the board is safe to plug in: +5V and +9V would land on the wrong pins.
- **J1's socket.** Fit it with its key at position 3, the third pad from the left. The
  solder joints carry the insertion force, so a bead of epoxy along the socket body and
  the board edge is worth adding. The socket's mating slot should line up with the board's
  mid-plane so the bus sits level with the ZX81's board; bend the tails evenly.
- **Slot socket.** The footprint assumes straight dip-solder tails on 0.2 in rows and a
  body about 66 x 7.9 mm. Check the socket you buy, especially the row spacing; many
  0.1 in card-edge sockets use 0.14 or 0.15 in instead.
- **Height.** A card's body starts at the top of its socket. J1's socket and the ZX81
  case sit in front of slot 1; the first card's components reach about 13 mm toward
  them at that height, so check the clearance in the case. Slot 1 is 22.86 mm from the
  front edge (`YF` in `gen_pcb.py`).
- **Current.** All three cards share the ZX81's +5V through a 0.6 mm run on B.Cu
  plus the In2 plane, and +9V through a 0.6 mm run. That is fine for the OpenSpand Card,
  which draws well under 0.5 A.
- **One supply at a time.** The DC jack connects straight to the ZX81's +9V pin, so it
  backfeeds the ZX81's own power input. Don't plug in the ZX81's original supply as well.
  D1 blocks a centre-negative supply, but only on the jack. Most of the ZX81's power goes through its own 7805, so check that it stays cool
  with the cards fitted.
- **DC jack part.** The footprint is the PJ-102AH layout. Check your jack's pins against
  it, and that it is 5.5/2.1 mm (some similar jacks are 2.0 or 2.5 mm).

## Ordering

Upload `hardware/fab/ZX81-Bus-gerbers.zip` to JLCPCB: 4 layers, 1.6 mm, and **gold fingers
with a 45° bevel** for the rear edge only. Ask for the front edge to be left square: J1's
socket is soldered to those pads. Everything is hand-soldered (`hand-solder.csv`): the
four 2 x 23 card-edge sockets (J1 straddling the front edge, J2-J4 in the slots), the
DC jack (J6) and D1 (an SMA part; its stripe, the cathode, faces the right edge).

## Regenerating

From `tools/`:

```bash
python3 gen_lib.py      # project library: slot socket, front straddle pads, rear fingers
python3 gen_sch.py
KPY=/Applications/KiCad/KiCad.app/Contents/Frameworks/Python.framework/Versions/Current/bin/python3
$KPY gen_pcb.py         # placement, every track, vias and pours
python3 export_fab.py
```

Edit `design.py` (connectivity) or the constants at the top of `gen_pcb.py` (slot pitch,
board size), and regenerate. `export_fab.py` refills the zones before it exports.

## License

CC BY-SA 4.0, like the OpenSpand Card it carries.

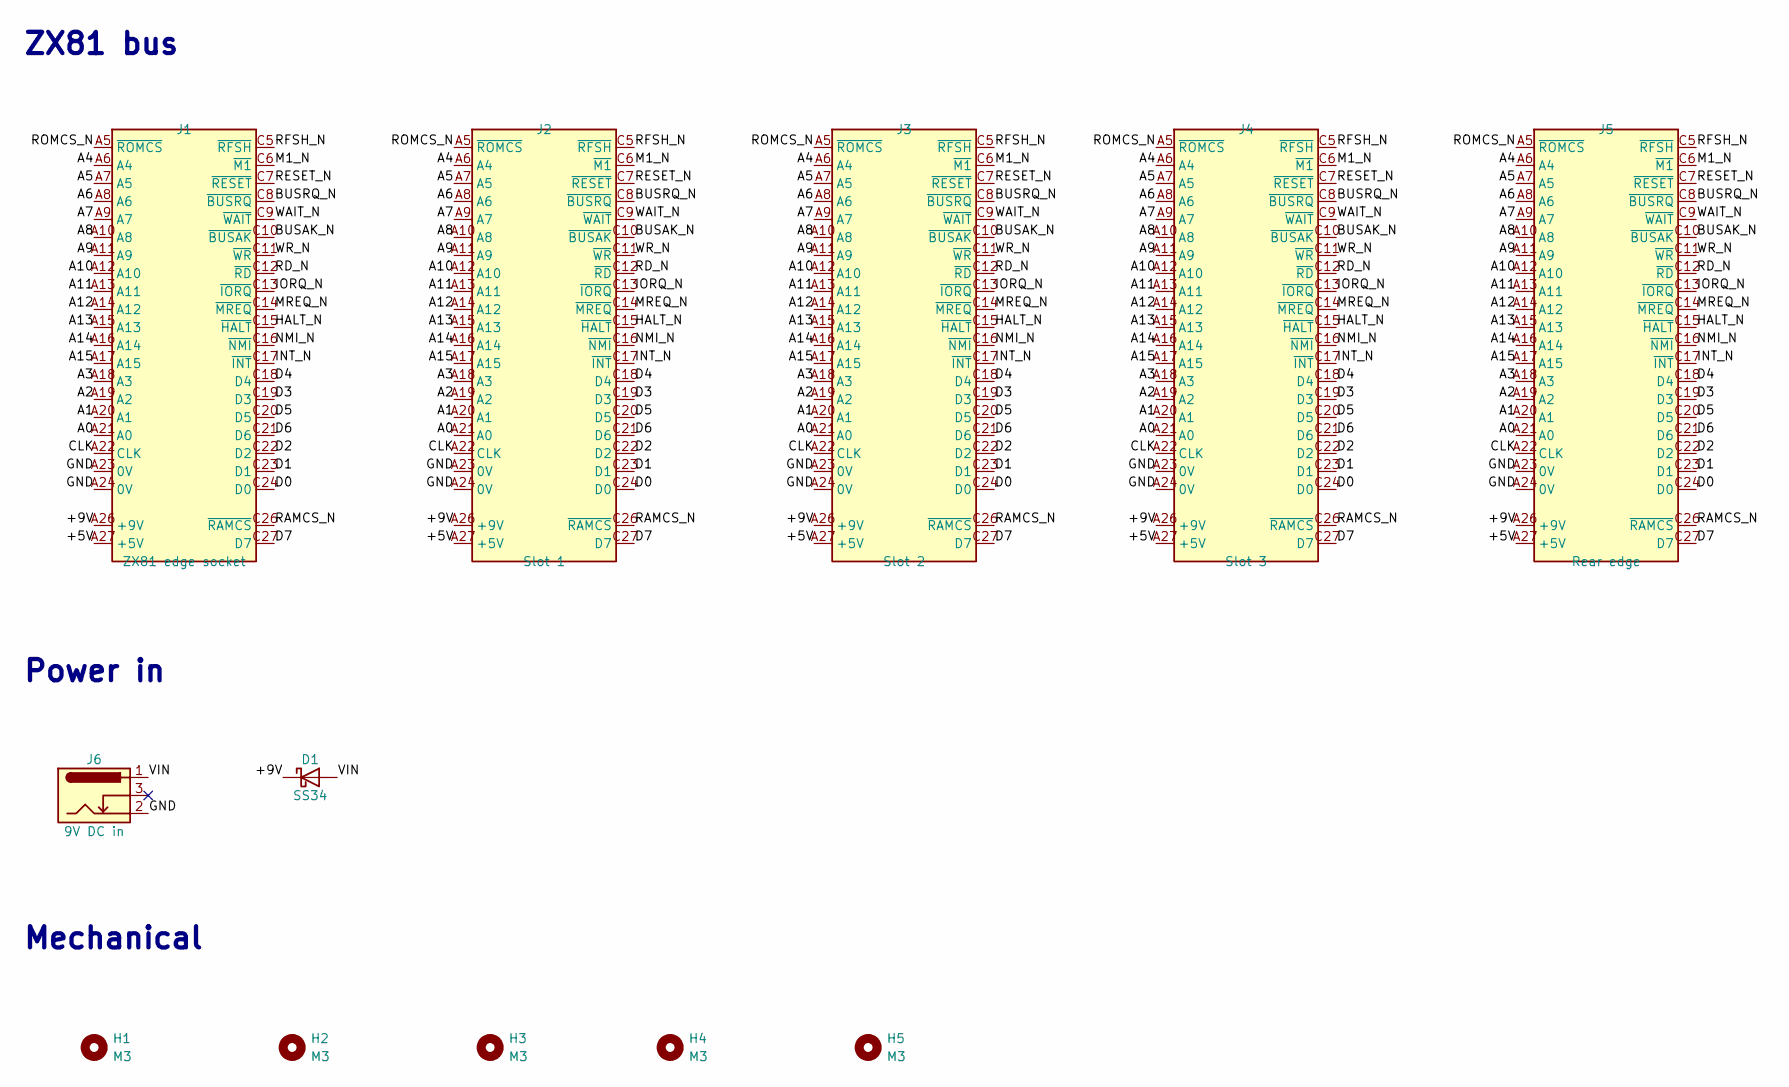
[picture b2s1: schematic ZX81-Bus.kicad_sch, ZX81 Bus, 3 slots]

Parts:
D1: SS34; D_SMA; LCSC C8678
H1, H2, H3, H4, H5: M3; MountingHole_3.2mm_M3
J1: ZX81 edge socket; ZX81_EdgeStraddle
J2: Slot 1; ZX81_Slot_2x23_P2.54mm_Row5.08mm
J3: Slot 2; ZX81_Slot_2x23_P2.54mm_Row5.08mm
J4: Slot 3; ZX81_Slot_2x23_P2.54mm_Row5.08mm
J5: Rear edge; ZX81_EdgeFingers_Rear
J6: 9V DC in; BarrelJack_CUI_PJ-102AH_Horizontal

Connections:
/+5V: J1.A27 (+5V), J2.A27 (+5V), J3.A27 (+5V), J4.A27 (+5V), J5.A27 (+5V)
/+9V: D1.1 (K), J1.A26 (+9V), J2.A26 (+9V), J3.A26 (+9V), J4.A26 (+9V), J5.A26 (+9V)
/A0: J1.A21 (A0), J2.A21 (A0), J3.A21 (A0), J4.A21 (A0), J5.A21 (A0)
/A1: J1.A20 (A1), J2.A20 (A1), J3.A20 (A1), J4.A20 (A1), J5.A20 (A1)
/A2: J1.A19 (A2), J2.A19 (A2), J3.A19 (A2), J4.A19 (A2), J5.A19 (A2)
/A3: J1.A18 (A3), J2.A18 (A3), J3.A18 (A3), J4.A18 (A3), J5.A18 (A3)
/A4: J1.A6 (A4), J2.A6 (A4), J3.A6 (A4), J4.A6 (A4), J5.A6 (A4)
/A5: J1.A7 (A5), J2.A7 (A5), J3.A7 (A5), J4.A7 (A5), J5.A7 (A5)
/A6: J1.A8 (A6), J2.A8 (A6), J3.A8 (A6), J4.A8 (A6), J5.A8 (A6)
/A7: J1.A9 (A7), J2.A9 (A7), J3.A9 (A7), J4.A9 (A7), J5.A9 (A7)
/A8: J1.A10 (A8), J2.A10 (A8), J3.A10 (A8), J4.A10 (A8), J5.A10 (A8)
/A9: J1.A11 (A9), J2.A11 (A9), J3.A11 (A9), J4.A11 (A9), J5.A11 (A9)
/A10: J1.A12 (A10), J2.A12 (A10), J3.A12 (A10), J4.A12 (A10), J5.A12 (A10)
/A11: J1.A13 (A11), J2.A13 (A11), J3.A13 (A11), J4.A13 (A11), J5.A13 (A11)
/A12: J1.A14 (A12), J2.A14 (A12), J3.A14 (A12), J4.A14 (A12), J5.A14 (A12)
/A13: J1.A15 (A13), J2.A15 (A13), J3.A15 (A13), J4.A15 (A13), J5.A15 (A13)
/A14: J1.A16 (A14), J2.A16 (A14), J3.A16 (A14), J4.A16 (A14), J5.A16 (A14)
/A15: J1.A17 (A15), J2.A17 (A15), J3.A17 (A15), J4.A17 (A15), J5.A17 (A15)
/BUSAK_N: J1.C10 (~BUSAK), J2.C10 (~BUSAK), J3.C10 (~BUSAK), J4.C10 (~BUSAK), J5.C10 (~BUSAK)
/BUSRQ_N: J1.C8 (~BUSRQ), J2.C8 (~BUSRQ), J3.C8 (~BUSRQ), J4.C8 (~BUSRQ), J5.C8 (~BUSRQ)
/CLK: J1.A22 (CLK), J2.A22 (CLK), J3.A22 (CLK), J4.A22 (CLK), J5.A22 (CLK)
/D0: J1.C24 (D0), J2.C24 (D0), J3.C24 (D0), J4.C24 (D0), J5.C24 (D0)
/D1: J1.C23 (D1), J2.C23 (D1), J3.C23 (D1), J4.C23 (D1), J5.C23 (D1)
/D2: J1.C22 (D2), J2.C22 (D2), J3.C22 (D2), J4.C22 (D2), J5.C22 (D2)
/D3: J1.C19 (D3), J2.C19 (D3), J3.C19 (D3), J4.C19 (D3), J5.C19 (D3)
/D4: J1.C18 (D4), J2.C18 (D4), J3.C18 (D4), J4.C18 (D4), J5.C18 (D4)
/D5: J1.C20 (D5), J2.C20 (D5), J3.C20 (D5), J4.C20 (D5), J5.C20 (D5)
/D6: J1.C21 (D6), J2.C21 (D6), J3.C21 (D6), J4.C21 (D6), J5.C21 (D6)
/D7: J1.C27 (D7), J2.C27 (D7), J3.C27 (D7), J4.C27 (D7), J5.C27 (D7)
/GND: J1.A23 (0V), J1.A24 (0V), J2.A23 (0V), J2.A24 (0V), J3.A23 (0V), J3.A24 (0V), J4.A23 (0V), J4.A24 (0V), J5.A23 (0V), J5.A24 (0V), J6.2
/HALT_N: J1.C15 (~HALT), J2.C15 (~HALT), J3.C15 (~HALT), J4.C15 (~HALT), J5.C15 (~HALT)
/INT_N: J1.C17 (~INT), J2.C17 (~INT), J3.C17 (~INT), J4.C17 (~INT), J5.C17 (~INT)
/IORQ_N: J1.C13 (~IORQ), J2.C13 (~IORQ), J3.C13 (~IORQ), J4.C13 (~IORQ), J5.C13 (~IORQ)
/M1_N: J1.C6 (~M1), J2.C6 (~M1), J3.C6 (~M1), J4.C6 (~M1), J5.C6 (~M1)
/MREQ_N: J1.C14 (~MREQ), J2.C14 (~MREQ), J3.C14 (~MREQ), J4.C14 (~MREQ), J5.C14 (~MREQ)
/NMI_N: J1.C16 (~NMI), J2.C16 (~NMI), J3.C16 (~NMI), J4.C16 (~NMI), J5.C16 (~NMI)
/RAMCS_N: J1.C26 (~RAMCS), J2.C26 (~RAMCS), J3.C26 (~RAMCS), J4.C26 (~RAMCS), J5.C26 (~RAMCS)
/RD_N: J1.C12 (~RD), J2.C12 (~RD), J3.C12 (~RD), J4.C12 (~RD), J5.C12 (~RD)
/RESET_N: J1.C7 (~RESET), J2.C7 (~RESET), J3.C7 (~RESET), J4.C7 (~RESET), J5.C7 (~RESET)
/RFSH_N: J1.C5 (~RFSH), J2.C5 (~RFSH), J3.C5 (~RFSH), J4.C5 (~RFSH), J5.C5 (~RFSH)
/ROMCS_N: J1.A5 (~ROMCS), J2.A5 (~ROMCS), J3.A5 (~ROMCS), J4.A5 (~ROMCS), J5.A5 (~ROMCS)
/VIN: D1.2 (A), J6.1
/WAIT_N: J1.C9 (~WAIT), J2.C9 (~WAIT), J3.C9 (~WAIT), J4.C9 (~WAIT), J5.C9 (~WAIT)
/WR_N: J1.C11 (~WR), J2.C11 (~WR), J3.C11 (~WR), J4.C11 (~WR), J5.C11 (~WR)

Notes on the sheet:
ZX81 bus
Power in
Mechanical

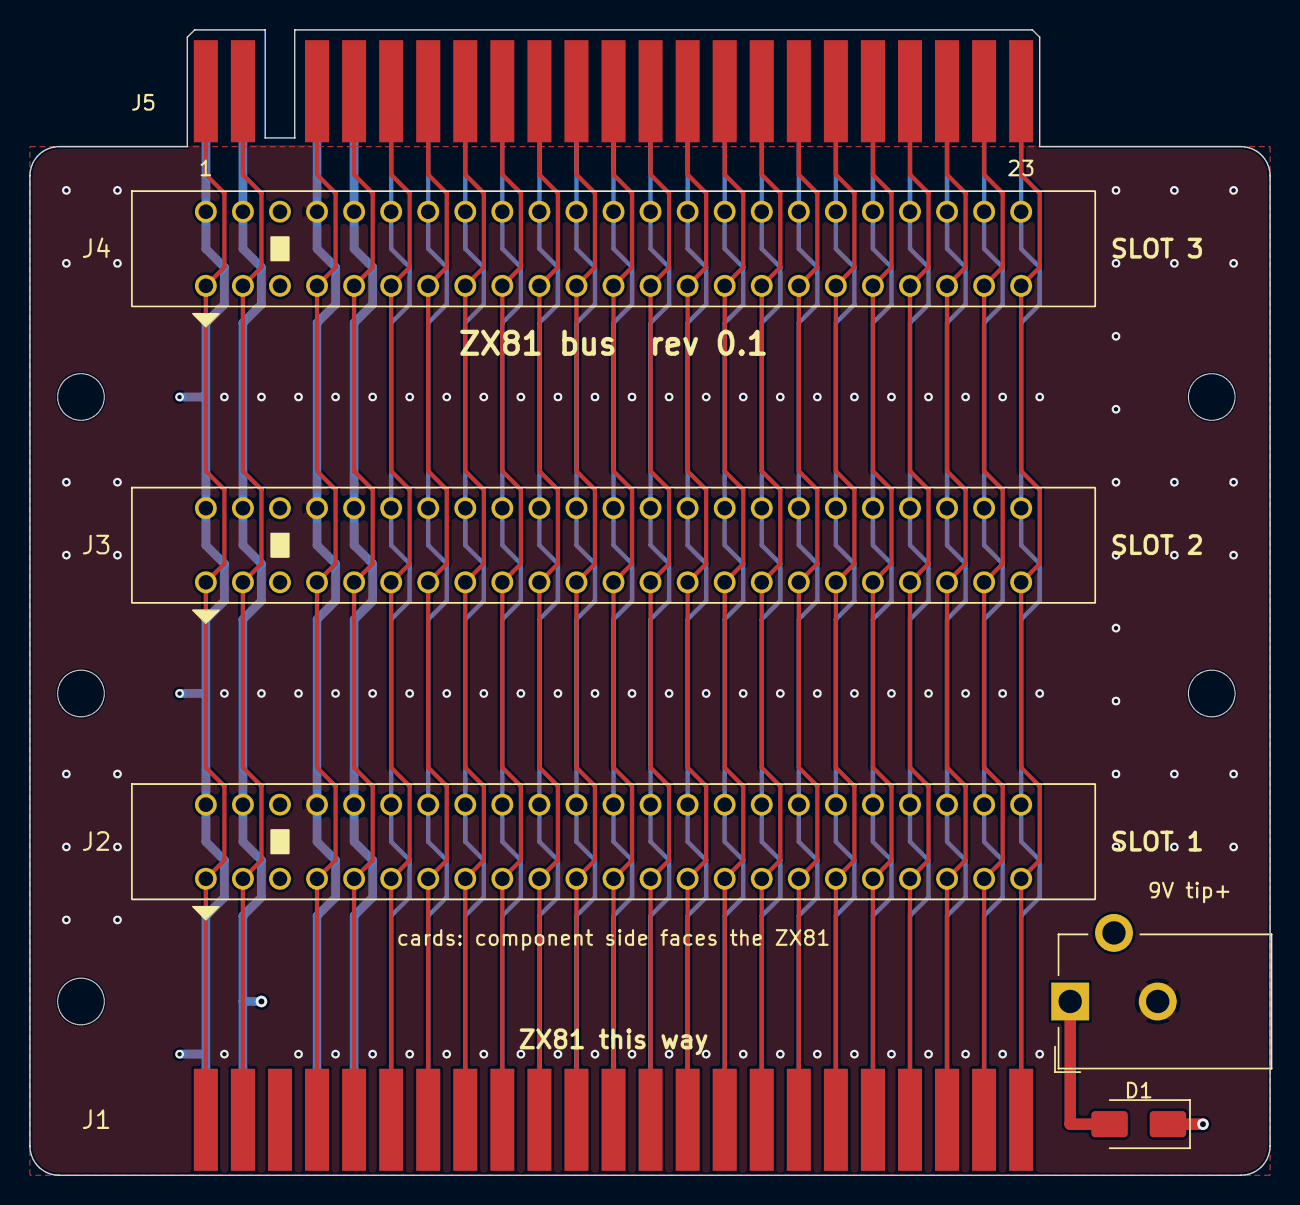
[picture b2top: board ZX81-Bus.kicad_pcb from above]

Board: 4 copper layers, 85.0 x 78.5 mm, 12 parts (0 on the bottom side), 44 nets.

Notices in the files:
bus/hardware/ZX81-Bus.kicad_sch:
Edge socket footprint from OpenSpand HW 1.3.1 by Adam Klotblixt & ZX-Team, CC BY-SA 4.0
card/hardware/OpenSpand-Card.kicad_pcb:
based on OpenSpand HW 1.3.1 (CC BY-SA 4.0)
card/hardware/OpenSpand-Card.kicad_sch:
Derived from OpenSpand HW 1.3.1 by Adam Klotblixt & ZX-Team, CC BY-SA 4.0
